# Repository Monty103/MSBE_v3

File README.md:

## MSBE_v3

An ultra-compact, low-power wearable audio device featuring bone-conduction technology, digital PDM voice capture, and multi-gesture touch controls.

---

## 🏗️ Core Component Architecture

| Component | Part Number | Function | Interface |
| :--- | :--- | :--- | :--- |
| **Main MCU** | **nRF5340-CLAA-R** | Dual-core Bluetooth 5.4 SoC (App & Network) | N/A |
| **PMIC** | **nPM1100** | Battery charging & high-efficiency power regulation | Analog/NTC |
| **Audio Driver** | **MAX98357A (x2)** | Class D I2S Amp for Bone Conduction Speakers | I2S |
| **Microphone** | **SPH18R1LM4H-1** | Digital MEMS Microphone for Voice/Calls | PDM |
| **Motion Sensor** | **BMA400** | Ultra-low power accelerometer (Proximity/Wake-up) | I2C |
| **Touch Controller**| **MPR121** | 12-Channel Capacitive Touch (Slider/Gestures) | I2C |

---

## ⚡ System Design Details

### 1. Processing (nRF5340)
The **Application Core** handles the I2S audio stream and gesture logic from the MPR121, while the **Network Core** manages the Bluetooth Low Energy (BLE) stack. 
* **Key Config:** Uses Port 1 for high-speed audio to isolate switching noise.

### 2. Audio Output (MAX98357A)
Two drivers are utilized to provide a stereo bone-conduction experience. These chips convert the digital I2S signal from the nRF5340 directly into analog power for the transducers.
* **Feature:** Filterless Class D, ideal for compact wearable PCB routing.

### 3. Voice Input (SPH18R1LM4H-1)
A high-performance PDM microphone. It operates in multiple power modes (Sleep, Low-Power, Normal) controlled dynamically by the nRF5340’s clock frequency to preserve battery life.

### 4. Power Management (nPM1100)
The PMIC ensures maximum battery life using a high-efficiency buck regulator. 
* **Safety:** Integrated Li-Po charger with JEITA thermal monitoring via a 10k NTC thermistor.
* **Form Factor:** Optimized for WLCSP-style compact assembly.

### 5. Interaction (BMA400 & MPR121)
* **BMA400:** Acts as a "wear-detect" sensor. It triggers an interrupt to wake the system when the headset is moved or put on.
* **MPR121:** Connected to a 3-pad copper slider on the PCB. It supports:
    * **Single/Double Tap:** Play/Pause/Assistant.
    * **Swipe Left/Right:** Volume and Track control via a state-machine on the nRF5340.

---

## 🛠️ Pin Mapping Summary

| Signal | nRF5340 Pin | Hardware Pin | Shared Bus |
| :--- | :--- | :--- | :--- |
| **I2C SCL** | **P0.04** | BMA400 (12) / MPR121 (3) | Yes |
| **I2C SDA** | **P0.05** | BMA400 (2) / MPR121 (4) | Yes |
| **PDM CLK** | **P0.26** | Mic (Clock) | No |
| **PDM DATA** | **P0.25** | Mic (Data) | No |
| **I2S SCK** | **P1.12** | MAX98357A (BCLK) | Yes |
| **I2S LRCLK** | **P1.13** | MAX98357A (WS) | Yes |
| **I2S SDOUT** | **P1.14** | MAX98357A (Din) | Yes |
| **BMA INT** | **P0.06** | BMA400 (INT1) | No |
| **Touch IRQ** | **P0.08** | MPR121 (IRQ) | No |

---

## 📋 Hardware Implementation Notes
* **Touch Slider:** 3-electrode design (ELE0, ELE1, ELE2) for swipe detection.
* **Mic Configuration:** SEL pin tied to GND for mono/left channel timing.
* **I2C Mode:** MPR121 CSB pin must be tied to VDDIO to enable I2C communication.
* **Power Rail:** All sensors and MCU peripherals are powered via the 1.8V VOUT from the nPM1100.

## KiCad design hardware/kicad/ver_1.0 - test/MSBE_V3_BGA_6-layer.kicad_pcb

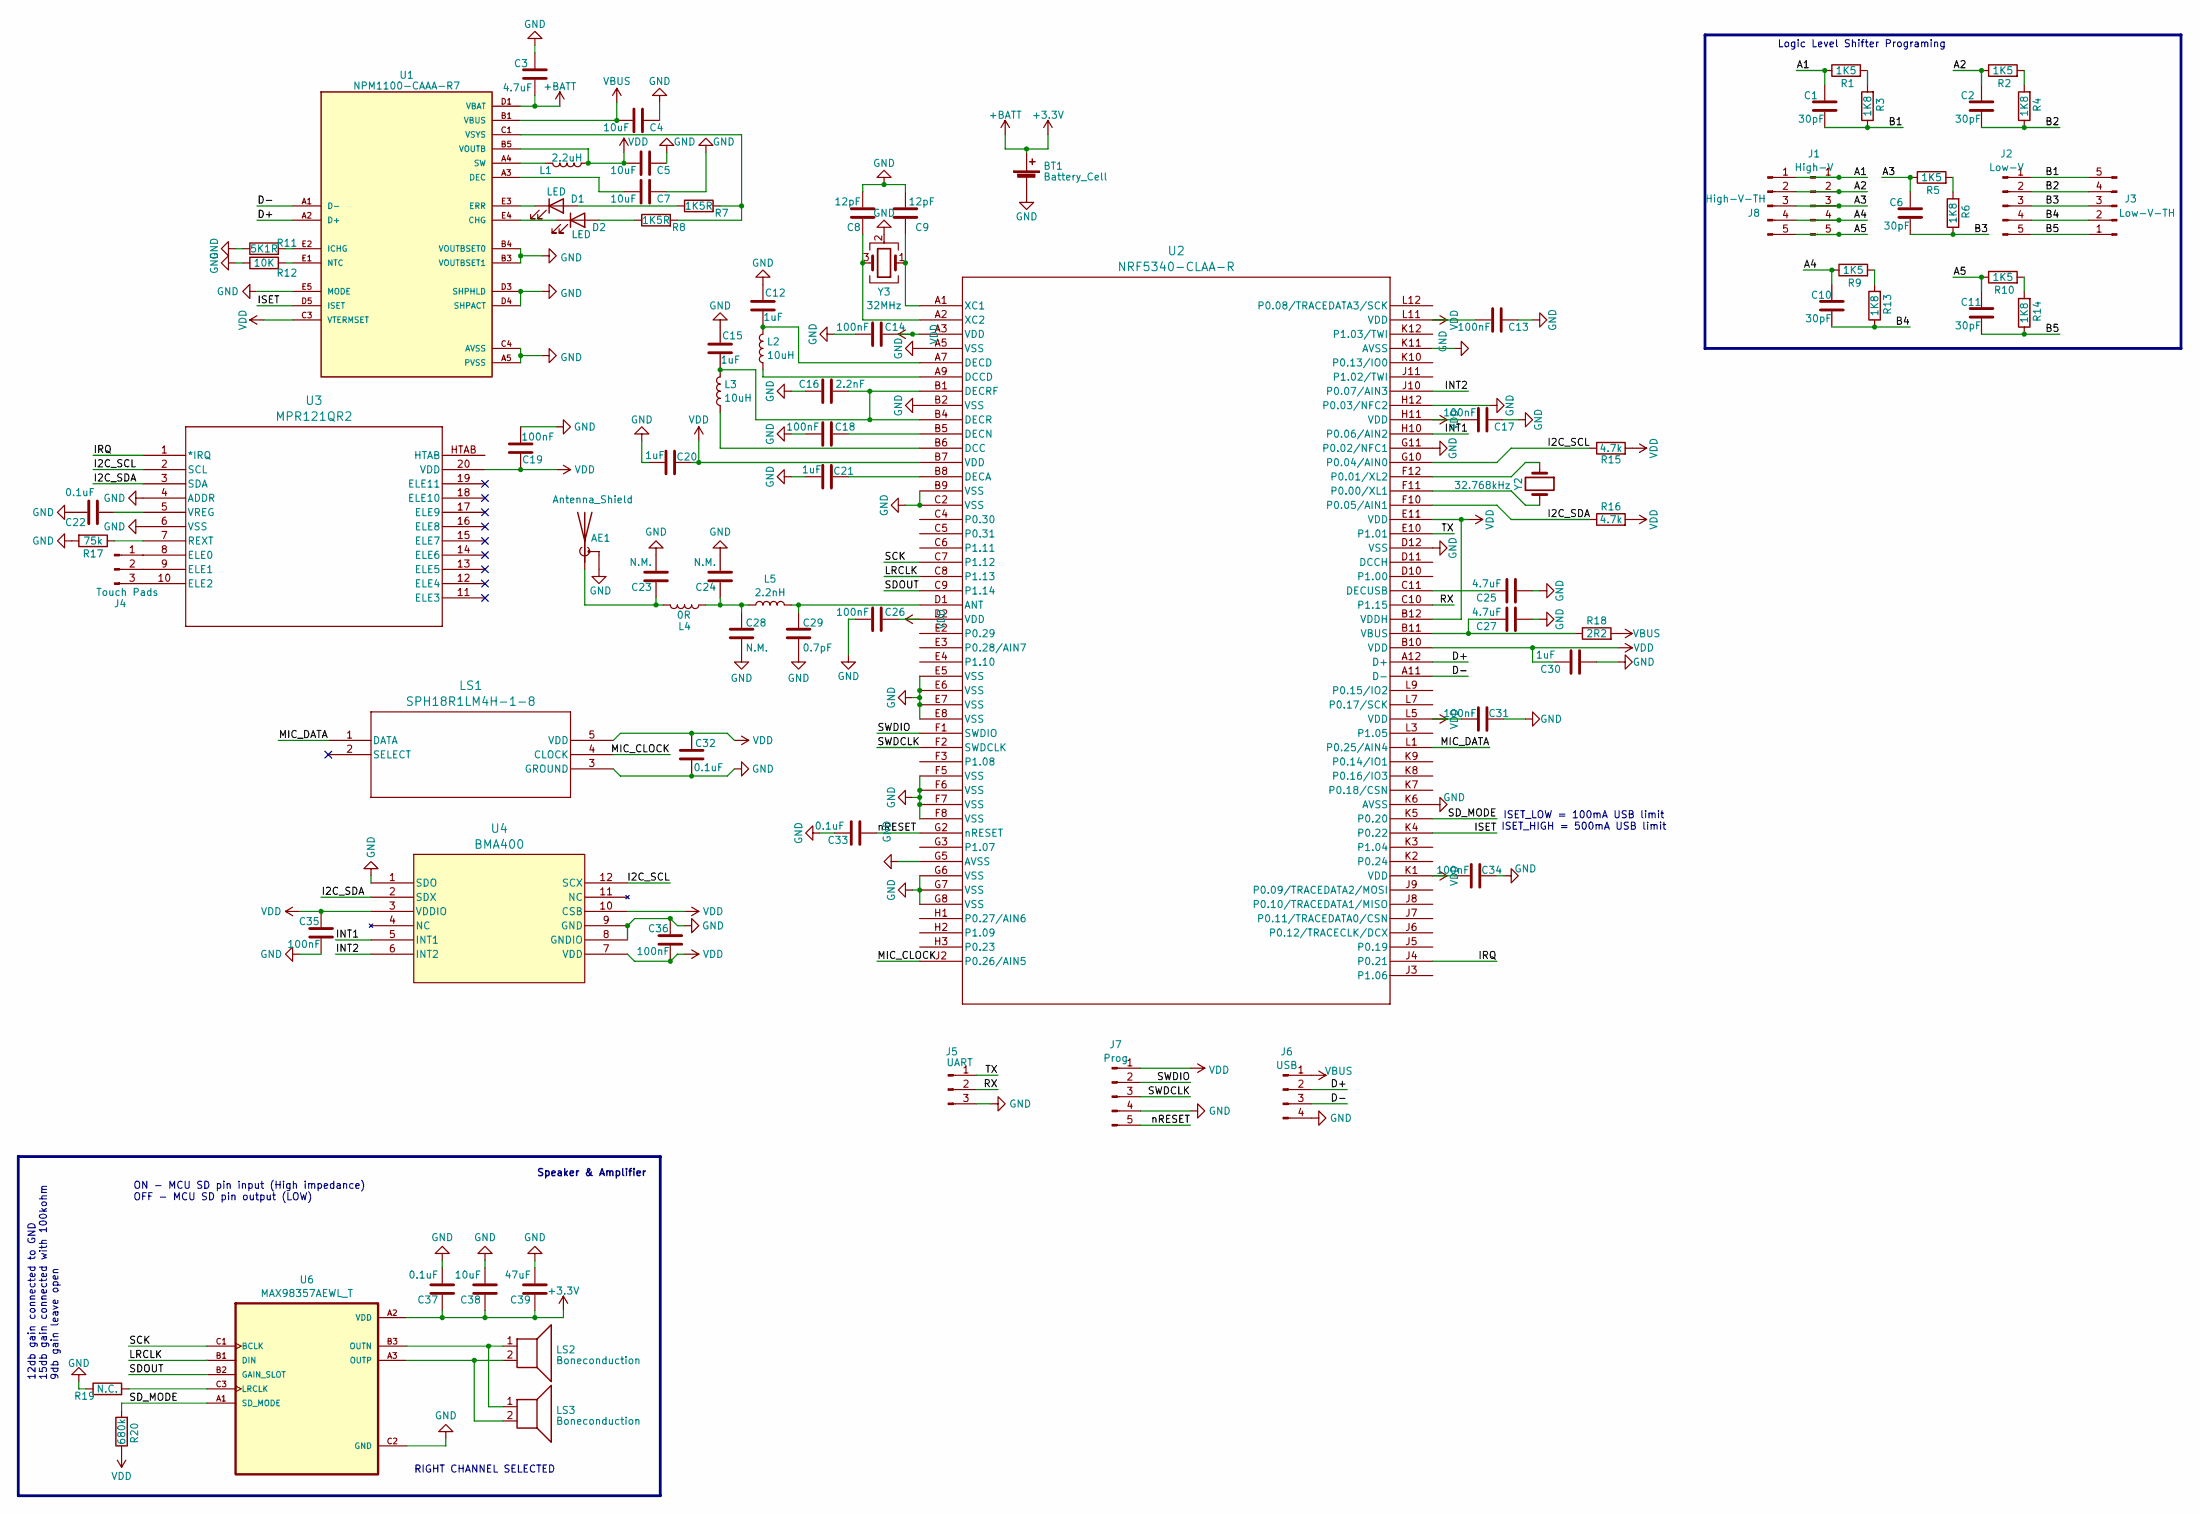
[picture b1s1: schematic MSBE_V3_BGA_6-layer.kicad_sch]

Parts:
AE1: Antenna_Shield; Texas_SWRA117D_2.4GHz_Left
BT1: Battery_Cell; Pad_3Pin_1.5x0.8mm
C1, C2, C6, C10, C11: 30pF; C_0402_1005Metric
C3, C25, C27: 4.7uF; C_0402_1005Metric
C4, C5, C7: 10uF; C_0402_1005Metric
C8, C9: 12pF; C_0402_1005Metric
C12, C15, C20, C21, C30: 1uF; C_0402_1005Metric
C13, C14, C17, C18, C19, C26, C31, C34, C35, C36: 100nF; C_0402_1005Metric
C16: 2.2nF; C_0402_1005Metric
C22, C32, C33, C37: 0.1uF; C_0402_1005Metric
C23, C24, C28: N.M.; C_0402_1005Metric
C29: 0.7pF; C_0402_1005Metric
C38: 10uF; C_0603_1608Metric
C39: 47uF; C_0603_1608Metric
D1, D2: LED; LED_0402_1005Metric
J1: High-V; Pad_4Pin_1.5x0.8mm
J2: Low-V; Pad_4Pin_1.5x0.8mm
J3: Low-V-TH; PinHeader_1x05_P2.54mm_Vertical
J4: Touch Pads; Pad_3Pin_1.5x0.8mm
J5: UART; Pad_3Pin_1.5x0.8mm
J6: USB; Pad_4Pin_1.5x0.8mm
J7: Prog; Pad_prog_4Pad
J8: High-V-TH; PinHeader_1x05_P2.54mm_Vertical
L1: 2.2uH; L_0402_1005Metric
L2, L3: 10uH; L_0402_1005Metric
L4: 0R; L_0402_1005Metric
L5: 2.2nH; L_0402_1005Metric
LS1: SPH18R1LM4H-1-8; MIC_SPH18R1LM4H_KNO
LS2, LS3: Boneconduction; Pad_2Pin_1.5x0.8mm
R1, R2, R5, R9, R10: 1K5; R_0402_1005Metric
R3, R4, R6, R13, R14: 1K8; R_0402_1005Metric
R7, R8: 1K5R; R_0402_1005Metric
R11: 5K1R; R_0402_1005Metric
R12: 10K; R_0402_1005Metric
R15, R16: 4.7k; R_0402_1005Metric
R17: 75k; R_0402_1005Metric
R18: 2R2; R_0402_1005Metric
R19: N.C.; R_0402_1005Metric
R20: 680k; R_0402_1005Metric
U1: NPM1100-CAAA-R7; NPM1100-CAAA-BGA25C40P5X5_207X207X52N
U2: NRF5340-CLAA-R; NRF5340_CLAA_R
U3: MPR121QR2; MPR121
U4: BMA400; QFN_BMA400_BOS
U6: MAX98357AEWL_T; MAX98357A_BGA9N40P3X3_134X143X69N
Y2: 32.768kHz; Pad_2Pin_1.5x0.8mm
Y3: 32MHz; ECS-160-10-37-JTN-TR_ECS

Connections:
+3.3V: BT1.1 (+), C3.2, C37.1, C38.1, C39.1, U1.D1 (VBAT), U1.D2 (VBAT), U6.A2 (VDD)
/A1: C1.1, J1.1, J8.1, R1.1; also elsewhere on the board
/A2: C2.1, J1.2, J8.2, R2.1; also elsewhere on the board
/A3: C6.1, J1.3, J8.3, R5.1; also elsewhere on the board
/A4: C10.1, J1.4, J8.4, R9.1; also elsewhere on the board
/A5: C11.1, J1.5, J8.5, R10.1; also elsewhere on the board
/B1: C1.2, J2.1, J3.5, R3.1; also elsewhere on the board
/B2: C2.2, J2.2, J3.4, R4.1; also elsewhere on the board
/B3: C6.2, J2.3, J3.3, R6.1; also elsewhere on the board
/B4: C10.2, J2.4, J3.2, R13.1; also elsewhere on the board
/B5: C11.2, J2.5, J3.1, R14.1; also elsewhere on the board
/D+: J6.2, U1.A2 (D+), U2.A12 (D+)
/D-: J6.3, U1.A1 (D-), U2.A11 (D-)
/I2C_SCL: R15.1, U2.G10 (P0.04/AIN0), U3.2 (SCL), U4.12 (SCX)
/I2C_SDA: R16.1, U2.F10 (P0.05/AIN1), U3.3 (SDA), U4.2 (SDX)
/INT1: U2.H10 (P0.06/AIN2), U4.5 (INT1)
/INT2: U2.J10 (P0.07/AIN3), U4.6 (INT2)
/IRQ: U2.J4 (P0.21), U3.1 (*IRQ)
/ISET: U1.D5 (ISET), U2.K4 (P0.22)
/LRCLK: U2.C8 (P1.13), U6.B1 (DIN)
/MIC_CLOCK: LS1.4 (CLOCK), U2.J2 (P0.26/AIN5)
/MIC_DATA: LS1.1 (DATA), U2.L1 (P0.25/AIN4)
/RX: J5.2, U2.C10 (P1.15)
/SCK: U2.C7 (P1.12), U6.C1 (BCLK)
/SDOUT: U2.C9 (P1.14), U6.B2 (GAIN_SLOT)
/SD_MODE: R20.2, U2.K5 (P0.20), U6.A1 (SD_MODE)
/SWDCLK: J7.3, U2.F2 (SWDCLK)
/SWDIO: J7.2, U2.F1 (SWDIO)
/TX: J5.1, U2.E10 (P1.01)
/nRESET: C33.1, J7.5, U2.G2 (nRESET)
GND: AE1.2 (Shield), BT1.2 (-), C3.1, C4.1, C5.1, C7.1, C8.2, C9.2, C12.1, C13.1, C14.2, C15.1, C16.1, C17.1, C18.2, C19.2, C20.2, C21.2, C22.2, C23.2, C24.2, C25.1, C26.2, C27.1, C28.2, C29.2, C30.1, C31.2, C32.2, C33.2, C34.2, C35.2, C36.1, C37.2, C38.2, C39.2, J5.3, J6.4, J7.4, LS1.3 (GROUND), R11.1, R12.1, R17.2, R19.1, U1.A5 (PVSS), U1.B3 (VOUTBSET1), U1.B4 (VOUTBSET0), U1.C4 (AVSS), U1.C5 (AVSS), U1.D3 (SHPHLD), U1.D4 (SHPACT), U1.E5 (MODE), U2.A5 (VSS), U2.B2 (VSS), U2.B9 (VSS), U2.C2 (VSS), U2.D12 (VSS), U2.E5 (VSS), U2.E6 (VSS), U2.E7 (VSS), U2.E8 (VSS), U2.F5 (VSS), U2.F6 (VSS), U2.F7 (VSS), U2.F8 (VSS), U2.G5 (AVSS), U2.G6 (VSS), U2.G7 (VSS), U2.G8 (VSS), U2.G11 (P0.02/NFC1), U2.H12 (P0.03/NFC2), U2.K6 (AVSS), U2.K11 (AVSS), U3.4 (ADDR), U3.6 (VSS), U4.1 (SDO), U4.8 (GNDIO), U4.9 (GND), U6.C2 (GND), Y3.2 (G), Y3.4 (G)
unnamed: AE1.1 (A), C23.1, L4.2
unnamed: C24.1, C28.1, L4.1, L5.1
unnamed: D1.2 (A), R7.1
unnamed: D1.1 (K), U1.E3 (ERR)
unnamed: D2.2 (A), R8.1
unnamed: D2.1 (K), U1.E4 (CHG)
unnamed: J4.1, U3.8 (ELE0)
unnamed: J4.2, U3.9 (ELE1)
unnamed: J4.3, U3.10 (ELE2)
unnamed: R1.2, R3.2
unnamed: R2.2, R4.2
unnamed: R5.2, R6.2
unnamed: R10.2, R14.2
unnamed: R9.2, R13.2
unnamed: C7.2, U1.A3 (DEC)
unnamed: R11.2, U1.E2 (ICHG)
unnamed: R12.2, U1.E1 (NTC)
unnamed: L1.2, U1.A4 (SW)
unnamed: C29.1, L5.2, U2.D1 (ANT)
unnamed: L3.1, U2.B6 (DCC)
unnamed: L2.1, U2.A9 (DCCD)
unnamed: C21.1, U2.B8 (DECA)
unnamed: C12.2, L2.2, U2.A7 (DECD)
unnamed: C18.1, U2.B5 (DECN)
unnamed: C15.2, C16.2, L3.2, U2.B1 (DECRF), U2.B4 (DECR)
unnamed: C25.2, U2.C11 (DECUSB)
unnamed: U2.F11 (P0.00/XL1), Y2.2
unnamed: U2.F12 (P0.01/XL2), Y2.1
unnamed: C27.2, R18.1, U2.B11 (VBUS)
unnamed: C9.1, U2.A1 (XC1), Y3.1
unnamed: C8.1, U2.A2 (XC2), Y3.3
unnamed: R17.1, U3.7 (REXT)
unnamed: C22.1, U3.5 (VREG)
unnamed: R19.2, U6.C3 (LRCLK)
unnamed: LS2.1, LS3.1, U6.B3 (OUTN)
unnamed: LS2.2, LS3.2, U6.A3 (OUTP)
VBUS: C4.2, J6.1, R18.2, U1.B1 (VBUS), U1.B2 (VBUS)
VDD: C5.2, C13.2, C14.1, C17.2, C19.1, C20.1, C26.1, C30.2, C31.1, C32.1, C34.1, C35.1, C36.2, J7.1, L1.1, LS1.5 (VDD), R15.2, R16.2, R20.1, U1.B5 (VOUTB), U1.C3 (VTERMSET), U2.A3 (VDD), U2.B7 (VDD), U2.B10 (VDD), U2.B12 (VDDH), U2.D2 (VDD), U2.E11 (VDD), U2.H11 (VDD), U2.K1 (VDD), U2.L5 (VDD), U2.L11 (VDD), U3.20 (VDD), U4.3 (VDDIO), U4.7 (VDD), U4.10 (CSB)
VSYS: R7.2, R8.2, U1.C1 (VSYS), U1.C2 (VSYS)

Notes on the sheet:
RIGHT CHANNEL SELECTED
Logic Level Shifter Programing
ISET_LOW = 100mA USB limit ISET_HIGH = 500mA USB limit
ON - MCU SD pin input (High impedance) OFF - MCU SD pin output (LOW)
12db gain connected to GND 15db gain connected with 100kohm 9db gain leave open
Speaker & Amplifier

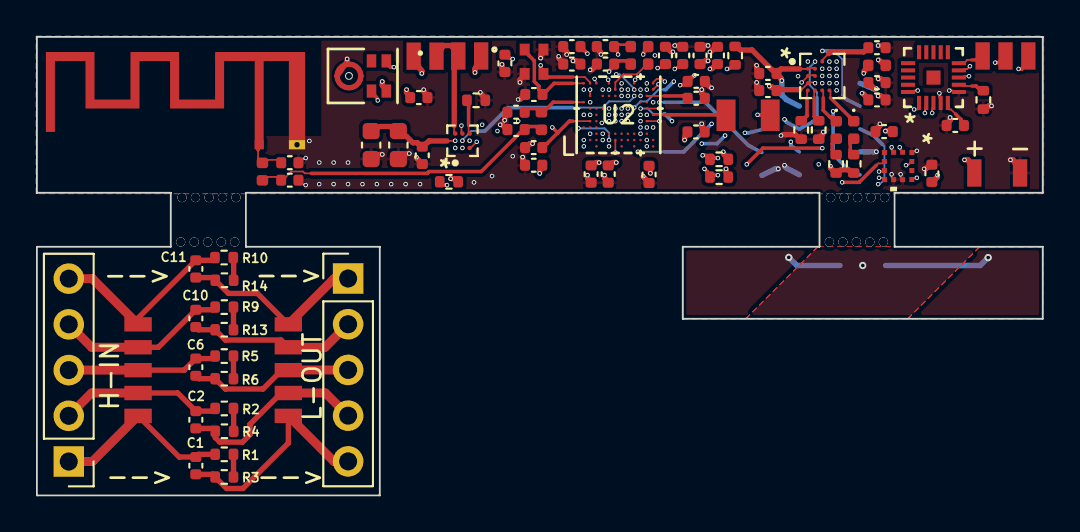
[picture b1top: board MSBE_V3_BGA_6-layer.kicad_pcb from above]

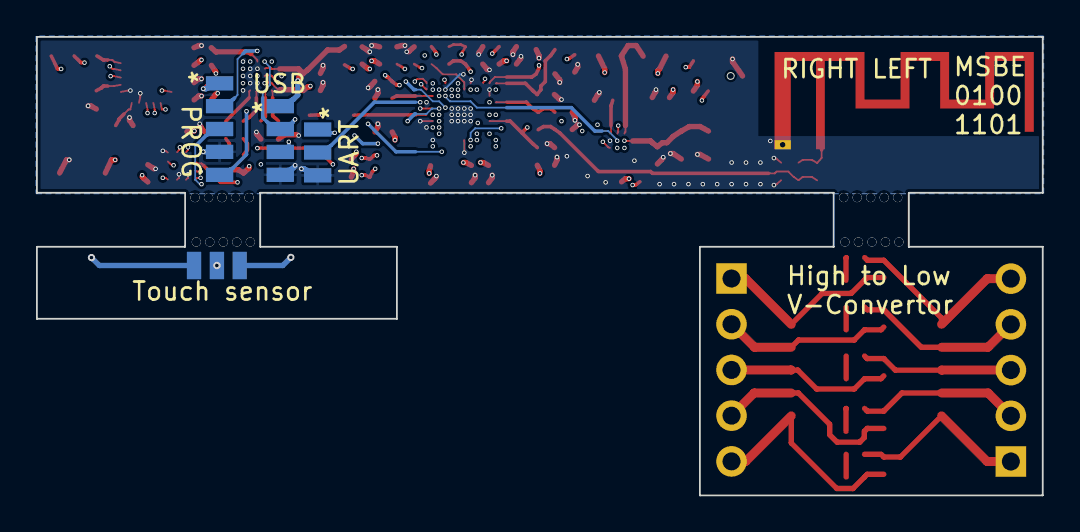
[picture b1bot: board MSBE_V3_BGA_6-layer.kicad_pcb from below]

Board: 6 copper layers, 55.9 x 25.5 mm, 86 parts (3 on the bottom side), 70 nets.

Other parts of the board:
H-IN: High-V-TH; PinHeader_1x05_P2.54mm_Vertical
L-OUT: Low-V-TH; PinHeader_1x05_P2.54mm_Vertical

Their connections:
/A1: H-IN.1; also elsewhere on the board
/A2: H-IN.2; also elsewhere on the board
/A3: H-IN.3; also elsewhere on the board
/A4: H-IN.4; also elsewhere on the board
/A5: H-IN.5; also elsewhere on the board
/B1: L-OUT.5; also elsewhere on the board
/B2: L-OUT.4; also elsewhere on the board
/B3: L-OUT.3; also elsewhere on the board
/B4: L-OUT.2; also elsewhere on the board
/B5: L-OUT.1; also elsewhere on the board

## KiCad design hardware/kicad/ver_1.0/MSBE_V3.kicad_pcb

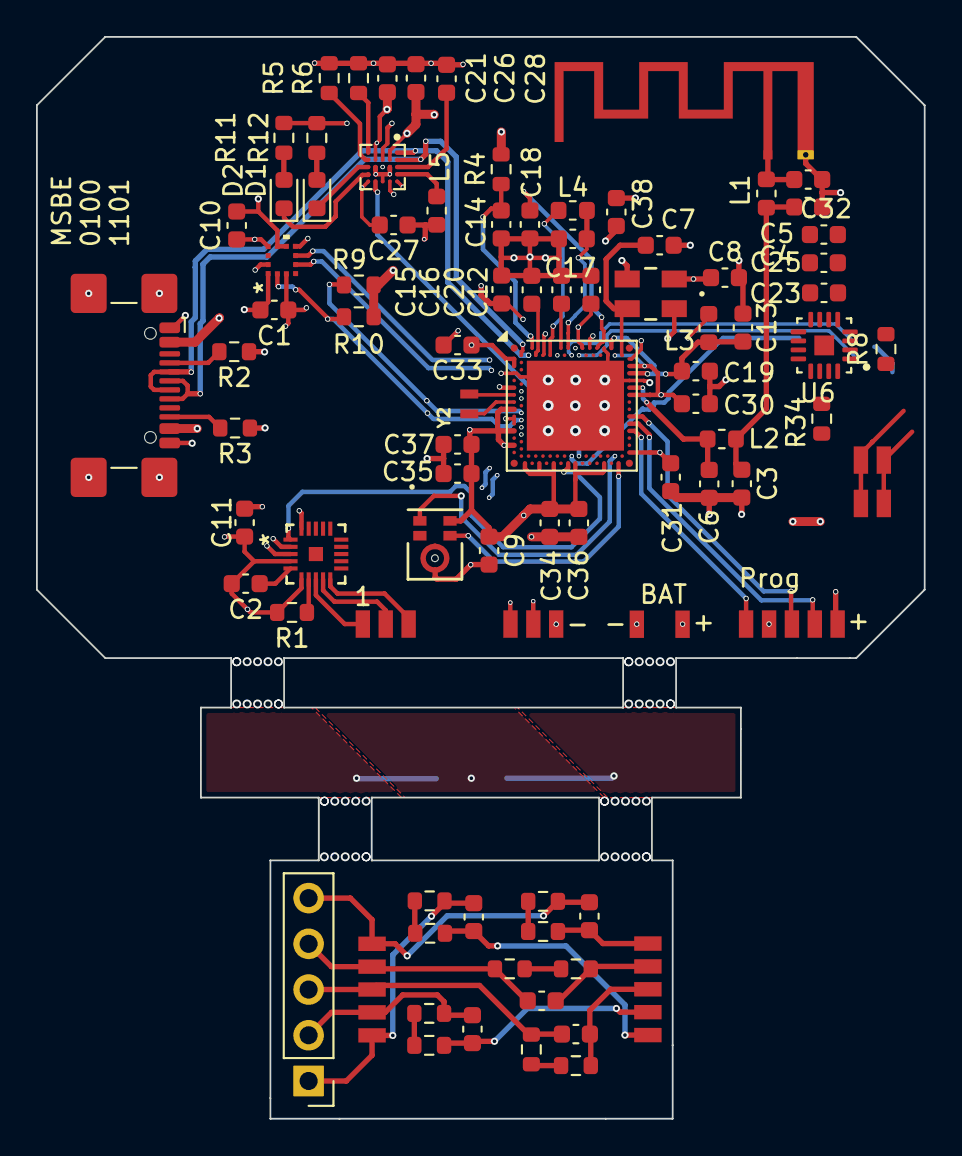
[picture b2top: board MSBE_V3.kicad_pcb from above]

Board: 4 copper layers, 49.3 x 60.1 mm, 88 parts (0 on the bottom side), 71 nets.

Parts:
AE1: Antenna_Shield; Texas_SWRA117D_2.4GHz_Left
BT1: Battery_Cell; Pad_3Pin_1.5x0.8mm
C1, C10, C11, C18, C30, C31, C33, C34, C35, C36, C37, C38: 100nF; C_0603_1608Metric
C2, C9, C23: 0.1uF; C_0603_1608Metric
C3, C4, C5: N.M.; C_0603_1608Metric
C6: 0.7pF; C_0603_1608Metric
C7, C8: 12pF; C_0603_1608Metric
C12, C13, C15, C17, C20: 1uF; C_0603_1608Metric
C14, C16, C21: 4.7uF; C_0603_1608Metric
C19: 2.2nF; C_0603_1608Metric
C25, C26, C27, C28: 10uF; C_0603_1608Metric
C32: 47uF; C_0603_1608Metric
C42, C45, C49, C50, C51: 30pF; C_0603_1608Metric
D1, D2: LED; LED_0603_1608Metric
J1: USB_C_Receptacle_USB2.0_16P; USB_C_Receptacle_GCT_USB4110
J2: Touch Pads; Pad_3Pin_1.5x0.8mm
J3: UART; Pad_3Pin_1.5x0.8mm
J4: Prog; Pad_prog_4Pad
J6: High-V; Pad_prog_4Pad
J8: Low-V; Pad_prog_4Pad
J9: Low-V-TH; PinHeader_1x05_P2.54mm_Vertical
L1: N.M.; L_0603_1608Metric
L2: 2.2nH; L_0603_1608Metric
L3, L4: 10uH; L_0603_1608Metric
L5: 2.2uH; L_0603_1608Metric
LS1: SPH18R1LM4H-1-8; MIC_SPH18R1LM4H_KNO
LS4, LS5: Boneconduction; Pad_2Pin_1.5x0.8mm
R1: 75k; R_0603_1608Metric
R2, R3, R5: 5K1R; R_0603_1608Metric
R4: 2R2; R_0603_1608Metric
R6: 10K; R_0603_1608Metric
R8: N.C.; R_0603_1608Metric
R9, R10: 4k7; R_0603_1608Metric
R11, R12: 1K5R; R_0603_1608Metric
R14, R15, R18, R22, R23: 1K5; R_0603_1608Metric
R16, R17, R19, R24, R25: 1K8; R_0603_1608Metric
R34: 680k; R_0603_1608Metric
U1: BMA400; QFN_BMA400_BOS
U2: MPR121QR2; MPR121
U3: NRF5340-QKAA-R; Nordic_AQFN-94-1EP_7x7mm_P0.4mm
U4: NPM1100-CAAA-R7; NPM1100-CAAA-BGA25C40P5X5_207X207X52N
U6: MAX98357AEWL_T; MAX98357AETE_QFN16
Y1: 32MHz; YSX321SL - 32Mhz Crystal
Y2: 32.768kHz; XTAL_ABS05-32.768KHZ-T

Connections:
+3.3V: BT1.1 (+), C1.1, C9.1, C10.2, C11.1, C12.1, C15.1, C21.2, C23.1, C25.1, C27.2, C30.1, C31.1, C32.1, C33.1, C34.1, C35.1, C36.1, C37.1, C38.1, J4.1, L5.1, LS1.5 (VDD), R9.2, R10.2, R34.1, U1.3 (VDDIO), U1.7 (VDD), U1.10 (CSB), U2.20 (VDD), U3.A19 (VDD), U3.AC1 (VDD), U3.AG1 (VDD), U3.AJ31 (VDD), U3.AL3 (VDD), U3.AL7 (VDD), U3.AL11 (VDD), U3.AL17 (VDD), U3.AL25 (VDD), U3.B8 (VDD), U3.B28 (VDD), U3.C1 (VDD), U3.E1 (VDDH), U3.E31 (VDD), U3.L1 (VDD), U3.N31 (VDD), U3.U1 (VDD), U4.B5 (VOUTB), U4.C3 (VTERMSET), U4.D1 (VBAT), U4.D2 (VBAT), U6.7 (VDD), U6.8 (VDD)
/A1: C42.1, J6.1, R14.1
/A2: C50.1, J6.2, R22.1
/A3: C49.1, J6.3, R18.1
/A4: C45.1, J6.4, R15.1
/A5: C51.1, J6.5, R23.1
/B1: C42.2, J8.1, J9.5, R16.1
/B2: C50.2, J8.2, J9.4, R24.1
/B3: C49.2, J8.3, J9.3, R19.1
/B4: C45.2, J8.4, J9.2, R17.1
/B5: C51.2, J8.5, J9.1, R25.1
/D+: J1.A6 (D+), J1.B6 (D+), U3.B2 (D+), U4.A2 (D+)
/D-: J1.A7 (D-), J1.B7 (D-), U3.B4 (D-), U4.A1 (D-)
/I2C_SCL: R9.1, U1.12 (SCX), U2.2 (SCL), U3.V2 (P0.04/AIN0)
/I2C_SDA: R10.1, U1.2 (SDX), U2.3 (SDA), U3.Y2 (P0.05/AIN1)
/INT1: U1.5 (INT1), U3.AB2 (P0.06/AIN2)
/INT2: U1.6 (INT2), U3.AD2 (P0.07/AIN3)
/IRQ: U2.1 (*IRQ), U3.AL15 (P0.21)
/ISET: U3.AK18 (P0.22), U4.D5 (ISET)
/LRCLK: U3.A17 (P1.13), U6.14 (LRCLK)
/MIC_CLOCK: LS1.4 (CLOCK), U3.AL29 (P0.26/AIN5)
/MIC_DATA: LS1.1 (DATA), U3.AK28 (P0.25/AIN4)
/RX: J3.2, U3.P2 (P1.01)
/SCK: U3.B18 (P1.12), U6.16 (BCLK)
/SDOUT: U3.B16 (P1.14), U6.1 (DIN)
/SD_MODE: R34.2, U3.AK16 (P0.20), U6.4 (~SD_MODE)
/SWDCLK: J4.3, U3.W31 (SWDCLK)
/SWDIO: J4.2, U3.AA31 (SWDIO)
/TX: J3.1, U3.M2 (P1.00)
/nRESET: J4.5, U3.AC31 (nRESET)
GND: AE1.2 (Shield), BT1.2 (-), C1.2, C2.2, C3.2, C4.2, C5.2, C6.2, C7.2, C8.2, C9.2, C10.1, C11.2, C12.2, C13.2, C14.2, C15.2, C16.2, C17.2, C18.2, C19.2, C20.2, C21.1, C23.2, C25.2, C26.1, C27.1, C28.1, C30.2, C31.2, C32.2, C33.2, C34.2, C35.2, C36.2, C37.2, C38.2, J1.A1 (GND), J1.A12 (GND), J1.B1 (GND), J1.B12 (GND), J1.S1 (SHIELD), J3.3, J4.4, LS1.3 (GROUND), R1.2, R2.1, R3.1, R5.1, R6.1, R8.1, U1.1 (SDO), U1.8 (GNDIO), U1.9 (GND), U2.4 (ADDR), U2.6 (VSS), U3.A25 (VSS), U3.AA1 (P0.03/NFC2), U3.B12 (VSS), U3.B26 (VSS), U3.G1 (VSS), U3.H2 (VSS), U3.J31 (VSS), U3.W1 (P0.02/NFC1), U4.A5 (PVSS), U4.B3 (VOUTBSET1), U4.B4 (VOUTBSET0), U4.C4 (AVSS), U4.C5 (AVSS), U4.D3 (SHPHLD), U4.D4 (SHPACT), U4.E5 (MODE), U6.3 (GND), U6.11 (GND), U6.15 (GND), U6.17 (EP), Y1.2
unnamed: AE1.1 (A), C5.1, L1.1
unnamed: C3.1, C4.1, L1.2, L2.1
unnamed: D1.2 (A), R12.1
unnamed: D1.1 (K), U4.E3 (ERR)
unnamed: D2.2 (A), R11.1
unnamed: D2.1 (K), U4.E4 (CHG)
unnamed: J1.A5 (CC1), R2.2
unnamed: J1.B5 (CC2), R3.2
unnamed: J2.1, U2.8 (ELE0)
unnamed: J2.2, U2.9 (ELE1)
unnamed: J2.3, U2.10 (ELE2)
unnamed: R14.2, R16.2
unnamed: R15.2, R17.2
unnamed: R18.2, R19.2
unnamed: R22.2, R24.2
unnamed: R23.2, R25.2
unnamed: R1.1, U2.7 (REXT)
unnamed: C2.1, U2.5 (VREG)
unnamed: L4.2, U3.B10 (DCCD)
unnamed: L3.2, U3.A21 (DCCR)
unnamed: C20.1, U3.A13 (DECA)
unnamed: C17.1, L4.1, U3.A15 (DECD)
unnamed: C18.1, U3.A23 (DECN)
unnamed: C13.1, C19.1, L3.1, U3.A27 (DECR), U3.G31 (DECRF)
unnamed: C16.1, U3.B6 (DECUSB)
unnamed: C14.1, R4.1, U3.A5 (VBUS)
unnamed: U3.N1 (P0.00/XL1), Y2.2
unnamed: U3.R1 (P0.01/XL2), Y2.1
unnamed: C6.1, L2.2, U3.L31 (ANT)
unnamed: C8.1, U3.C31 (XC1), Y1.1
unnamed: C7.1, U3.B30 (XC2), Y1.3
unnamed: C28.2, U4.A3 (DEC)
unnamed: R5.2, U4.E2 (ICHG)
unnamed: R6.2, U4.E1 (NTC)
unnamed: L5.2, U4.A4 (SW)
unnamed: R8.2, U6.2 (GAIN_SLOT)
unnamed: LS4.1, LS5.1, U6.10 (OUTN)
unnamed: LS4.2, LS5.2, U6.9 (OUTP)
VBUS: C26.2, J1.A4 (VBUS), J1.A9 (VBUS), J1.B4 (VBUS), J1.B9 (VBUS), R4.2, U4.B1 (VBUS), U4.B2 (VBUS)
VSYS: R11.2, R12.2, U4.C1 (VSYS), U4.C2 (VSYS)

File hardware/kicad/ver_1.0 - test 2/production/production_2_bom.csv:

Designator,Footprint,Quantity,Value,LCSC Part #
"_2, ",,2,,
AE1,Texas_SWRA117D_2.4GHz_Left,1,Antenna_Shield,
BT1,Pad_3Pin_1.5x0.8mm,1,Battery_Cell,
"C1, C10, C11, C18, C30, C31, C33, C34, C35, C36, C37, C38",0603,12,100nF,
"C12, C13, C15, C17, C20",0603,5,1uF,
"C14, C16, C21",0603,3,4.7uF,
C19,0603,1,2.2nF,
"C2, C23, C9",0603,3,0.1uF,
"C25, C26, C27, C28",0603,4,10uF,
"C3, C4, C5, L1",0603,4,N.M.,
C32,0603,1,47uF,
"C42, C45, C49, C50, C51",0603,5,30pF,
C6,0603,1,0.7pF,
"C7, C8",0603,2,12pF,
"D1, D2",0603,2,LED,
J1,USB_C_Receptacle_GCT_USB4110,1,USB_C_Receptacle_USB2.0_16P,
J2,Pad_3Pin_1.5x0.8mm,1,Touch Pads,
J3,Pad_3Pin_1.5x0.8mm,1,UART,
J4,Pad_prog_4Pad,1,Prog,
J6,Pad_prog_4Pad,1,High-V,
J8,Pad_prog_4Pad,1,Low-V,
J9,PinHeader_1x05_P2.54mm_Vertical,1,Low-V-TH,
L2,0603,1,2.2nH,
"L3, L4",0603,2,10uH,
L5,0603,1,2.2uH,
LS1,MIC_SPH18R1LM4H_KNO,1,SPH18R1LM4H-1-8,
"LS4, LS5",Pad_2Pin_1.5x0.8mm,2,Boneconduction,
R1,0603,1,75k,
"R10, R9",0603,2,4k7,
"R11, R12",0603,2,1K5R,
"R14, R15, R18, R22, R23",0603,5,1K5,
"R16, R17, R19, R24, R25",0603,5,1K8,
"R2, R3, R5",0603,3,5K1R,
R34,0603,1,680k,
R4,0603,1,2R2,
R6,0603,1,10K,
R8,0603,1,N.C.,
U1,QFN_BMA400_BOS,1,BMA400,
U2,MPR121,1,MPR121QR2,
U3,Nordic_AQFN-94-1EP_7x7mm_P0.4mm,1,NRF5340-QKAA-R,
U4,NPM1100-CAAA-BGA25C40P5X5_207X207X52N,1,NPM1100-CAAA-R7,
U6,MAX98357A_BGA9N40P3X3_134X143X69N,1,MAX98357AEWL_T,
Y1,YSX321SL - 32Mhz Crystal,1,32MHz,
Y2,XTAL_ABS05-32.768KHZ-T,1,32.768kHz,

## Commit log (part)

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2025-10-10 new refferences added
2025-10-10 added SDK folder
2025-11-07 added new references
2025-11-12 added new firmware reference website
2025-11-12 update references
2026-03-12 Added kicad schematic and routed all. Next needed to make PCB
2026-05-01 updated all
2026-05-07 new stuff added
2026-05-12 modified schematic only
2026-05-26 new chip package
2026-05-27 updated schematic QFN
2026-06-02 update 2
